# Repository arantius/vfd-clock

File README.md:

A six digit clock based on the IV-22 Vacuum Fluorescent Display tube.

A learning project for me, using vacuum fluorescent display tubes and the STM32 processor for the first time.

I personally built one of these, and ended up with lots of spare parts.
I sold a _very limited_ number of kits, made up mostly of those spares.
I have no plans to assemble nor sell any further kits.
If you are interested in building this clock yourself, check out the Bill of Materials below, and the issues tab.

# Bill of Materials

| Part | Reference(s) | Value | Example Manufacturer Part Number |
| ---- | ------------ | ----- | -------------------------------- |
| Battery Holder | BT1 | n/a | BU2032SM-BT-GTR |
| Chip Capacitor (0603) | C1, C2 | 4pF | - |
| Electrolytic Capacitor | C3, C4, C5, C6 | 47μF | 25YXF47MEFC5X11 |
| Chip Capacitor (0603) | C7 | 330pF | n/a |
| DC Jack | CON2 | - | EJ508A |
| DC Plug | - | - | PP3-002A |
| Diode | D1 | - | STPS130A |
| Inductor | L1 | 68μH | RCH8011NP-680L |
| Transistor | Q1, Q2 | - | MMBT4403LT1G |
| Resistor | R1 | 0.22Ω | LR1LJR22 |
| Chip Resistor (0603) | R2 | 12.4kΩ | - |
| Chip Resistor (0603) | R3 | 41.2kΩ | - |
| Chip Resistor (0603) | R4, R5 | 1kΩ | - |
| Variable Resistor | RV1 | 22kΩ | PVA2A223A01R00 [#1](https://github.com/arantius/vfd-clock/issues/1) |
| Piezo Speaker | SP1 | - | AT-1224-TWT-5V-2-R [#2](https://github.com/arantius/vfd-clock/issues/2) |
| Tactile Switch | SW1, SW2, SW3, SW4 | - | FSM6JSMA |
| Microcontroller | U1 | Maple Mini | - |
| 7-Segment Driver (16-SOIC) | U2, U3, U4, U5, U6, U7 | - | CD4056BM96 |
| Boost Regulator (8-SOIC) | U8 | - | MC34063ACD-TR |
| Volt Level Shifter (16-TSSOP) | U9, U10 | - | CD4504BPWR |
| VFD Display Tube | V1, V2, V3, V4, V5, V6 | - | IV-22 (a.k.a. IN-22, IИ-22) |
| Watch Crystal | X1 | 32.7680kHz | CFS-20632768DZBB |
| Optional GPS | - | - | NEO-6M |

Notes:
 * The official [Baite store on Aliexpress ](https://www.aliexpress.com/store/product/x/213957_1400682373.html) is a reliable source of cheap clone Maple Mini boards.
 * You'll also need 72 single-pin sockets for the tubes, these are most commonly/affordably available on eBay.  Look for "nixie pin socket".  (They're $0.20 each from DigiKey, but as low as $0.05 each in quantity from eBay.)  These sockets raise the tube off the board so that the vaccum seal "nipple" has some room.  Plus the ability to remove and replace tubes is nice!
 * The optional GPS module, if used, should have an 0.1" four pin header of: Vcc, RX, TX, GND in that order.  I used a "Ublox NEO-6M" module.
 * The battery (and its) holder is optional.  If you don't mind losing the time when you unplug you don't need it.

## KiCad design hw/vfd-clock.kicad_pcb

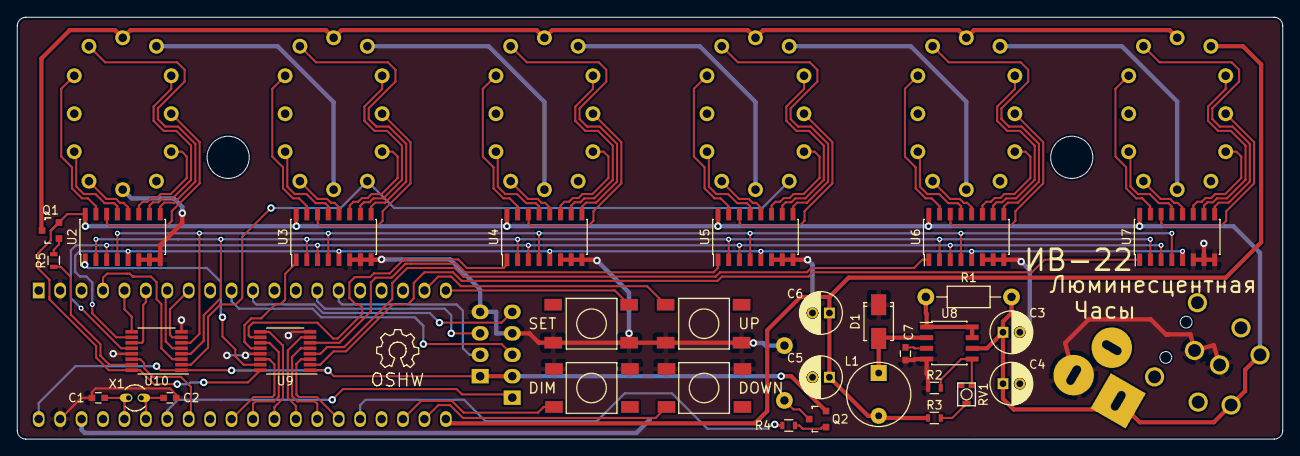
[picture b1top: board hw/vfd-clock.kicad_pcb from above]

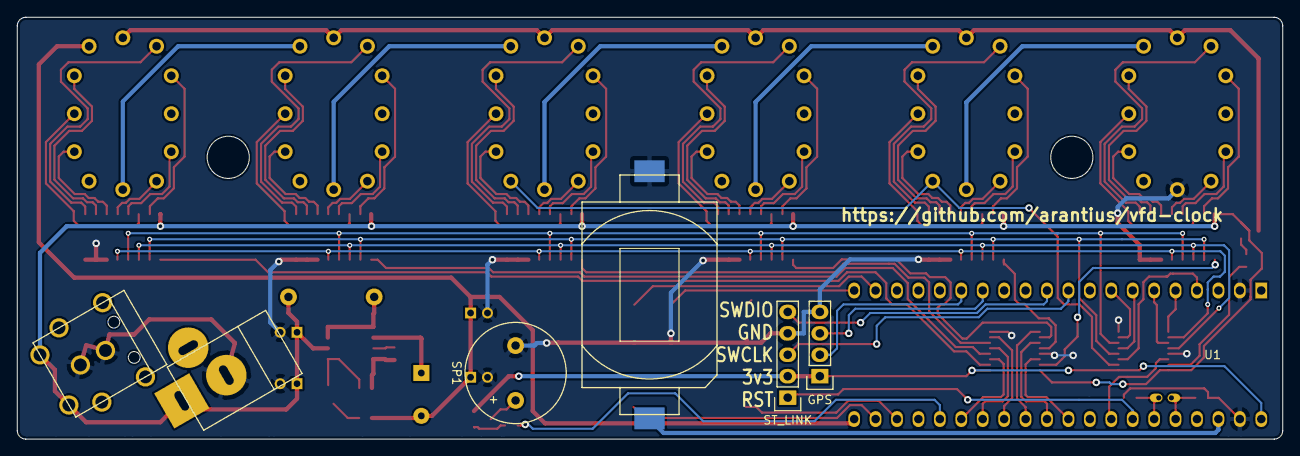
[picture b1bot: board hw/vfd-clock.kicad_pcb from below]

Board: 2 copper layers, 150.0 x 50.0 mm, 46 parts (7 on the bottom side), 97 nets.

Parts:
BT1: COIN_BATT; BATT2032-1060TR
C1, C2: 4p; C_0603
C3, C4, C5, C6: 47u; C_Radial_D5_L11_P2
C7: 330p; C_0603
CON1: BARREL_JACK_2; JACK_ALIM
CON2: BARREL_JACK_2; OCT_JACK
D1: DIODESCH; Diode-SMA_Standard
L1: 68u; INDUCTOR_V
M1, M2: MountingHole_4-5mm; MountingHole_5mm
P1: ST_LINK; Pin_Header_Straight_1x05
P2: GPS; Pin_Header_Straight_1x04
Q1, Q2: PNP; MMBT4403L
R1: 0.22; Resistor_Horizontal_RM10mm
R2: 12.4k; R_0603
R3: 54.9k; R_0603
R4, R5: 1k; R_0603
RV1: 4k7; PVA2_POT
SP1: SPEAKER; AT-1224-TWT
SW1: SET; SMD_TACT_6mm
SW2: UP; SMD_TACT_6mm
SW3: DOWN; SMD_TACT_6mm
SW4: DIM; SMD_TACT_6mm
U1: Maple_Mini_(BTE14-07)
U2, U3, U4, U5, U6, U7: CD4056; SOIC-16_3.9x9.9mm_Pitch1.27mm
U8: MC34063; SOIC-8_3.9x4.9mm_Pitch1.27mm
U9, U10: CD4504; TSSOP-16_4.4x5mm_Pitch0.65mm
V1, V2, V3, V4, V5, V6: IV-22; DISP_IV-22_1PIN_SOCKET
X1: CRYSTAL; Crystal_Round_Vertical_3mm_BigPad

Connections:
/3v3: P1.2, P2.1, Q2.1, U1.40, U9.1, U10.1
/7v2: C5.1, C6.1, L1.2, R3.2, U1.21, V6.1
/19v5: C3.1, C4.1, CON1.1, CON2.1, Q1.1, R1.1, U2.16, U3.16, U4.16, U5.16, U6.16, U7.16, U8.6, U9.16, U10.16
/A1: U2.9, V1.11
/A2: U3.9, V2.11
/A3: U4.9, V3.11
/A4: U5.9, V4.11
/A5: U6.9, V5.11
/A6: U7.9, V6.11
/B1: U2.10, V1.2
/B2: U3.10, V2.2
/B3: U4.10, V3.2
/B4: U5.10, V4.2
/B5: U6.10, V5.2
/B6: U7.10, V6.2
/BTN_DIM: SW4.1, U1.23
/BTN_DN: SW3.1, U1.22
/BTN_SET: SW1.1, U1.20
/BTN_UP: SW2.1, U1.19
/BUZ: R4.2, U1.25
/C1: U2.11, V1.4
/C2: U3.11, V2.4
/C3: U4.11, V3.4
/C4: U5.11, V4.4
/C5: U6.11, V5.4
/C6: U7.11, V6.4
/D1: U2.12, V1.7
/D2: U3.12, V2.7
/D3: U4.12, V3.7
/D4: U5.12, V4.7
/D5: U6.12, V5.7
/D6: U7.12, V6.7
/DAH: U2.5, U3.5, U4.5, U5.5, U6.5, U7.5, U10.10
/DAL: U1.5, U10.9
/DBH: U2.3, U3.3, U4.3, U5.3, U6.3, U7.3, U10.12
/DBL: U1.6, U10.11
/DCH: U2.2, U3.2, U4.2, U5.2, U6.2, U7.2, U10.4
/DCL: U1.7, U10.5
/DDH: U2.4, U3.4, U4.4, U5.4, U6.4, U7.4, U10.6
/DDL: U1.8, U10.7
/DPH: U10.2, V2.5, V4.5
/DPL: U1.4, U10.3
/E1: U2.13, V1.8
/E2: U3.13, V2.8
/E3: U4.13, V3.8
/E4: U5.13, V4.8
/E5: U6.13, V5.8
/E6: U7.13, V6.8
/F1: U2.15, V1.10
/F2: U3.15, V2.10
/F3: U4.15, V3.10
/F4: U5.15, V4.10
/F5: U6.15, V5.10
/F6: U7.15, V6.10
/FIL1: V1.1, V2.6
/FIL2: V2.1, V3.6
/FIL3: V3.1, V4.6
/FIL4: V4.1, V5.6
/FIL5: V5.1, V6.6
/G1: U2.14, V1.3
/G2: U3.14, V2.3
/G3: U4.14, V3.3
/G4: U5.14, V4.3
/G5: U6.14, V5.3
/G6: U7.14, V6.3
/GND: BT1.2, C1.2, C2.2, C3.2, C4.2, C5.2, C6.2, C7.1, CON1.2, CON2.2, D1.1, P1.4, P2.4, R2.2, SP1.2, SW1.2, SW2.2, SW3.2, SW4.2, U1.2, U1.39, U2.6, U2.7, U2.8, U3.6, U3.7, U3.8, U4.6, U4.7, U4.8, U5.6, U5.7, U5.8, U6.6, U6.7, U6.8, U7.6, U7.7, U7.8, U8.4, U9.8, U9.13, U10.8, U10.13, V1.6
/GPS_RX: P2.2, U1.15
/GPS_TX: P2.3, U1.14
/GRID: Q1.3, V1.12, V2.12, V3.12, V4.12, V5.12, V6.12
/GRIDH: R5.2, U10.15
/GRIDL: U1.33, U10.14
/REG_HI: R1.2, U8.1, U8.7, U8.8
/RST: P1.1, U1.34
/STROBE1H: U2.1, U9.15
/STROBE1L: U1.31, U9.14
/STROBE2H: U3.1, U9.12
/STROBE2L: U1.30, U9.11
/STROBE3H: U4.1, U9.10
/STROBE3L: U1.29, U9.9
/STROBE4H: U5.1, U9.6
/STROBE4L: U1.28, U9.7
/STROBE5H: U6.1, U9.4
/STROBE5L: U1.27, U9.5
/STROBE6H: U7.1, U9.2
/STROBE6L: U1.26, U9.3
/SWCLK: P1.3, U1.10
/SWDIO: P1.5, U1.11
/Vbat: BT1.1, U1.38
unnamed: C1.1, U1.36, X1.1
unnamed: C2.1, U1.35, X1.2
unnamed: C7.2, U8.3
unnamed: D1.2, L1.1, U8.2
unnamed: Q1.2, R5.1
unnamed: Q2.2, R4.1
unnamed: Q2.3, SP1.1
unnamed: R2.1, RV1.1, U8.5
unnamed: R3.1, RV1.2

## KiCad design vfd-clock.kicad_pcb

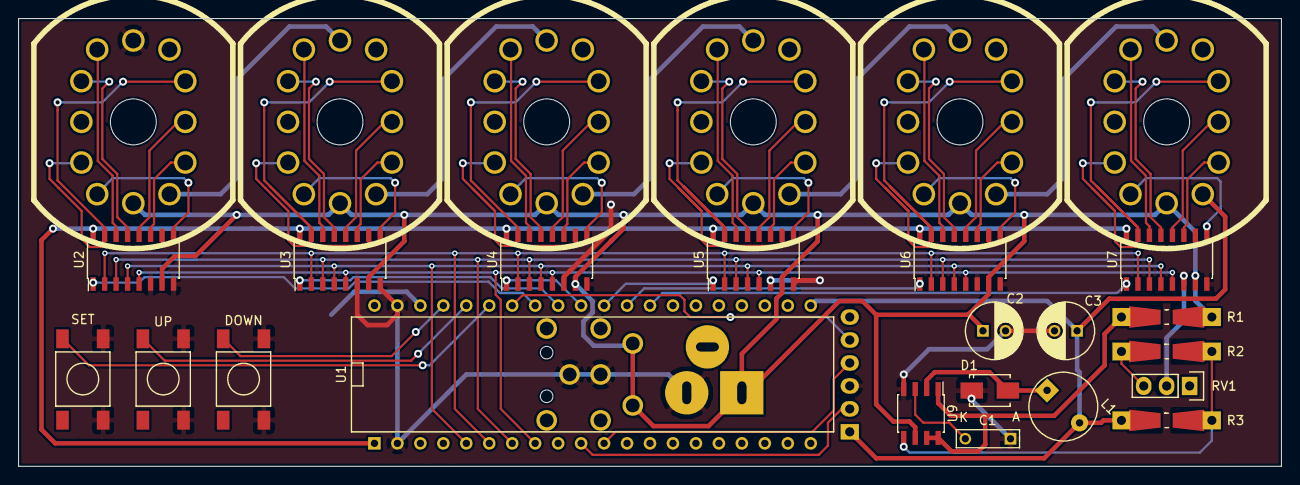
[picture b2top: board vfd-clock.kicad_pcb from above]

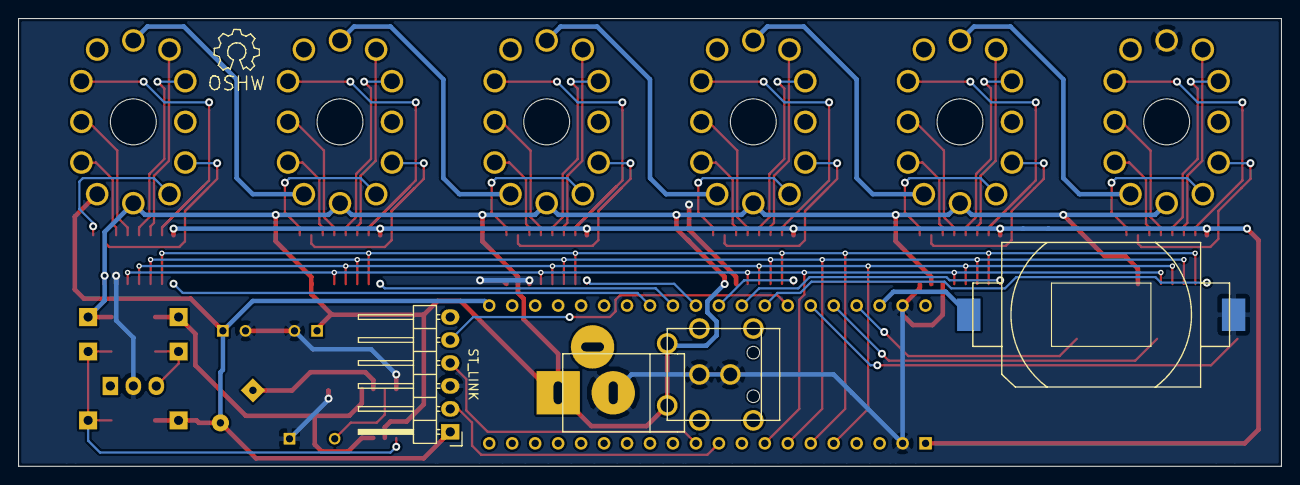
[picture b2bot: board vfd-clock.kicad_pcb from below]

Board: 2 copper layers, 139.7 x 49.5 mm, 30 parts (4 on the bottom side), 73 nets.

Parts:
BT1: COIN_BATT; BATT2032-1060TR
C1: 330p; C_Rect_L7_W2_P5
C2, C3: 100u; C_Radial_D6.3_L11.2_P2.5
CON1: BARREL_JACK_2; JACK_ALIM
CON2: BARREL_JACK_2; OCT_JACK
D1: DIODESCH; Diode-SMA_Standard
L1: 68u; INDUCTOR_V
P1: ST_LINK; Pin_Header_Angled_1x06
R1: 0.22; Resistor_SMD+THTuniversal_0805to1206_RM10_HandSoldering
R2: 12k; Resistor_SMD+THTuniversal_0805to1206_RM10_HandSoldering
R3: 59.5k; Resistor_SMD+THTuniversal_0805to1206_RM10_HandSoldering
RV1: 1k; Pin_Header_Straight_1x03
SW1: SET; SMD_TACT_6mm
SW2: UP; SMD_TACT_6mm
SW3: DOWN; SMD_TACT_6mm
U1: Maple_Mini_(BTE14-07); DIP-40__600
U2, U3, U4, U5, U6, U7: CD4056; SOIC-16_3.9x9.9mm_Pitch1.27mm
U9: MC34063; SOIC-8_3.9x4.9mm_Pitch1.27mm
V1, V2, V3, V4, V5, V6: IV-22; DISP_IV-22_SOCKET

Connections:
/3v3: U1.1, U2.16, U3.16, U4.16, U5.16, U6.16, U7.16
/7v2: C3.1, L1.2, P1.1, R3.1, U1.21, V6.5
/19v5: C2.1, CON1.1, CON2.1, R1.1, U2.7, U3.7, U4.7, U5.7, U6.7, U7.7, U9.6, V1.6, V2.6, V3.6, V4.6, V5.6, V6.6
/BTN_DN: SW3.1, U1.37
/BTN_SET: SW1.1, U1.35
/BTN_UP: SW2.1, U1.36
/DA: U1.8, U2.5, U3.5, U4.5, U5.5, U6.5, U7.5
/DB: U1.7, U2.3, U3.3, U4.3, U5.3, U6.3, U7.3
/DC: U1.6, U2.2, U3.2, U4.2, U5.2, U6.2, U7.2
/DD: U1.5, U2.4, U3.4, U4.4, U5.4, U6.4, U7.4
/FIL1: V1.5, V2.12
/FIL2: V2.5, V3.12
/FIL3: V3.5, V4.12
/FIL4: V4.5, V5.12
/FIL5: V5.5, V6.12
/GND: BT1.2, C1.1, C2.2, C3.2, CON1.2, CON2.2, D1.1, P1.3, RV1.2, SW1.2, SW2.2, SW3.2, U1.2, U1.39, U2.6, U2.8, U3.6, U3.8, U4.6, U4.8, U5.6, U5.8, U6.6, U6.8, U7.6, U7.8, U9.4, V1.12
/REG_HI: R1.2, U9.1, U9.7, U9.8
/RST: P1.5, U1.34
/STROBE1: U1.33, U2.1
/STROBE2: U1.32, U3.1
/STROBE3: U1.31, U4.1
/STROBE4: U1.30, U5.1
/STROBE5: U1.29, U6.1
/STROBE6: U1.28, U7.1
/SWCLK: P1.2, U1.10
/SWDIO: P1.4, U1.11
/Vbat: BT1.1, U1.38
unnamed: C1.2, U9.3
unnamed: D1.2, L1.1, U9.2
unnamed: R2.1, RV1.3
unnamed: R2.2, R3.2, U9.5
unnamed: U2.9, V1.7
unnamed: U2.10, V1.8
unnamed: U2.11, V1.4
unnamed: U2.12, V1.3
unnamed: U2.13, V1.10
unnamed: U2.14, V1.11
unnamed: U2.15, V1.2
unnamed: U3.9, V2.7
unnamed: U3.10, V2.8
unnamed: U3.11, V2.4
unnamed: U3.12, V2.3
unnamed: U3.13, V2.10
unnamed: U3.14, V2.11
unnamed: U3.15, V2.2
unnamed: U4.9, V3.7
unnamed: U4.10, V3.8
unnamed: U4.11, V3.4
unnamed: U4.12, V3.3
unnamed: U4.13, V3.10
unnamed: U4.14, V3.11
unnamed: U4.15, V3.2
unnamed: U5.9, V4.7
unnamed: U5.10, V4.8
unnamed: U5.11, V4.4
unnamed: U5.12, V4.3
unnamed: U5.13, V4.10
unnamed: U5.14, V4.11
unnamed: U5.15, V4.2
unnamed: U6.9, V5.7
unnamed: U6.10, V5.8
unnamed: U6.11, V5.4
unnamed: U6.12, V5.3
unnamed: U6.13, V5.10
unnamed: U6.14, V5.11
unnamed: U6.15, V5.2
unnamed: U7.9, V6.7
unnamed: U7.10, V6.8
unnamed: U7.11, V6.4
unnamed: U7.12, V6.3
unnamed: U7.13, V6.10
unnamed: U7.14, V6.11
unnamed: U7.15, V6.2

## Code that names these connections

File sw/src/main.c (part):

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#define BTN_MAPLE_PIN GPIO_Pin_8

#define BTN_PORT GPIOB
#define BTN_DIM_PIN GPIO_Pin_10
#define BTN_SET_PIN GPIO_Pin_12
#define BTN_UP_PIN GPIO_Pin_13
#define BTN_DN_PIN GPIO_Pin_11
typedef enum {BTN_NONE, BTN_MAPLE, BTN_UP, BTN_DOWN, BTN_DIM, BTN_SET} ButtonId;
#define BTN_ALL_PINS (BTN_MAPLE_PIN|BTN_DIM_PIN|BTN_SET_PIN|BTN_UP_PIN|BTN_DN_PIN)

#define DATA_PORT GPIOB
#define DA_PIN GPIO_Pin_6
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#define DP_PIN GPIO_Pin_7

#define STROBE_PORT GPIOA
#define STROBE1_PIN GPIO_Pin_2
#define STROBE2_PIN GPIO_Pin_3
#define STROBE3_PIN GPIO_Pin_4
#define STROBE4_PIN GPIO_Pin_5
#define STROBE5_PIN GPIO_Pin_6
#define STROBE6_PIN GPIO_Pin_7
#define STROBE_ALL_PINS ( \
    STROBE1_PIN | STROBE2_PIN | STROBE3_PIN \
    | STROBE4_PIN | STROBE5_PIN | STROBE6_PIN)

#define GRID_PORT GPIOA
#define GRID_PIN GPIO_Pin_0
#define BUZ_PORT GPIOB
#define BUZ_PIN GPIO_Pin_0

#define DIGIT_L 10
#define DIGIT_H 11
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// Amount to change the current time by, when setting this digit up/down.
const uint16_t gSettingChange[6] = {0, 3600, 600, 60, 10, 1};
const uint16_t gStrobePins[6] = {
    STROBE1_PIN, STROBE2_PIN, STROBE3_PIN,
    STROBE4_PIN, STROBE5_PIN, STROBE6_PIN};

// \\ // \\ // \\ // \\ // \\ // \\ // \\ // \\ // \\ // \\ // \\ // \\ // \\ //

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  GPIO_InitStructure.GPIO_Speed = GPIO_Speed_10MHz;

  // Port A, output.
  GPIO_InitStructure.GPIO_Pin = STROBE1_PIN | STROBE2_PIN | STROBE3_PIN
      | STROBE4_PIN | STROBE5_PIN | STROBE6_PIN;
  GPIO_InitStructure.GPIO_Mode = GPIO_Mode_Out_PP;  // Push-pull output.
  GPIO_Init(GPIOA, &GPIO_InitStructure);

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  GPIO_InitStructure.GPIO_Mode = GPIO_Mode_IPD;  // Input, pull down.
  GPIO_Init(GPIOB, &GPIO_InitStructure);
  GPIO_InitStructure.GPIO_Pin =
      BTN_DIM_PIN | BTN_SET_PIN | BTN_UP_PIN | BTN_DN_PIN;
  GPIO_InitStructure.GPIO_Mode = GPIO_Mode_IPU;  // Input, pull up.
  GPIO_Init(GPIOB, &GPIO_InitStructure);
  // Port B, output.
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  GPIO_InitTypeDef GPIO_InitStructure;
  GPIO_InitStructure.GPIO_Speed = GPIO_Speed_10MHz;
  GPIO_InitStructure.GPIO_Mode = GPIO_Mode_AF_PP;
  GPIO_InitStructure.GPIO_Pin = GRID_PIN;
  GPIO_Init(GRID_PORT, &GPIO_InitStructure);
  GPIO_InitStructure.GPIO_Pin = BUZ_PIN;
  GPIO_Init(BUZ_PORT, &GPIO_InitStructure);

  // Time base configuration;
  TIM_TimeBaseInitTypeDef  TIM_TimeBaseStructure;
  TIM_TimeBaseStructure.TIM_ClockDivision = TIM_CKD_DIV1;
  TIM_TimeBaseStructure.TIM_CounterMode = TIM_CounterMode_Up;

  // Grid PWM is on PA0 (D11), this is timer 2 channel 1.
  // 72MHz system clock / 1800 / 80 = 500Hz
  TIM_TimeBaseStructure.TIM_Period = 80;
  TIM_TimeBaseStructure.TIM_Prescaler = 1800;
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  uint8_t btnPressed = 0;
  uint16_t btns = GPIO_ReadInputData(BTN_PORT) & BTN_ALL_PINS;
  if ((btns & BTN_MAPLE_PIN) == BTN_MAPLE_PIN) btnPressed = BTN_MAPLE;
  else if ((btns & BTN_DIM_PIN) == 0) btnPressed = BTN_DIM;
  else if ((btns & BTN_DN_PIN) == 0) btnPressed = BTN_DOWN;
  else if ((btns & BTN_UP_PIN) == 0) btnPressed = BTN_UP;
  else if ((btns & BTN_SET_PIN) == 0) btnPressed = BTN_SET;
  if (btnPressed && gButtonPending == btnPressed) {
    if (gButtonDebounce > 10) {
      // Button already activated, still held, do nothing.
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  GPIO_WriteBit(LED_PORT, LED_PIN, RESET);

  // Disable buzzer.
  GPIO_WriteBit(BUZ_PORT, BUZ_PIN, RESET);
  TIM_Cmd(TIM3, DISABLE);

  backupLoad();
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
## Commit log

2015-05-31 initial commit; with maple mini library component
2015-05-31 add CD4504 level shifters
2015-05-31 add CD4543
2015-05-31 add IV-22
2015-05-31 various bits of the schematic wired up
2015-05-31 remove backup file
2015-06-01 schematic progress, board positioning
2015-06-01 tubes, data bus: routed
2015-06-01 first fully routed revision
2015-06-01 second redundant power connector footprint
    (I expect to only ever populate one or the other.)
2015-06-01 add buttons to set time
2015-06-05 lots of rerouting, buttons, part switches
    surface mount!
2015-07-14 create 'hw' directory beside 'sw'
2015-07-15 Major hardware rework.
    With discrete voltage level shifters, buzzer, pins for a GPS module
    addon.
2015-07-15 slim main.c
2015-07-15 Blinky project base.
    "New project" template from GNU Arm Eclipse plugins.
2015-07-15 set counter value AND interrupt once per second!!!
2015-07-15 Set RTC prescaler correctly.
    Add an extra #if branch because it has to come after WaitForSynchro()!
2015-07-15 use mini's button to set a counter value
2015-07-15 crappy working version via systick
2015-07-15 start to do button/display I/O
    Only thing that works for sure is the LED test
2015-07-15 rtc init? doesn't fire interrupts
2015-07-15 duh, enable GPIO port B !
2015-07-15 Doc note.
2015-07-15 add sw LICENSE
2015-07-15 more minimal, RTC interrupt fires
    way too often though???
2015-07-15 interrupt handler only sets a few global vars
2015-07-15 get rid of unused main() args
    and the noisy GCC pragmas to silence the warnings
2015-07-16 various small tweaks
    including switch the VFD tube outline from silkscreen to fab layer
2015-07-16 Fix VFD pinout.
2015-07-16 VFD trace tweak, label font size
2015-07-17 last level shifter output lights decimal points
    specifically the 2nd and 4th, i.e. between the hours/minutes and
    minutes/seconds
2015-07-19 mount holes, tweaks to ground fill, gerbers
2015-07-19 Sketchup framework for stand design
2015-07-19 Complete design for plastic stand.
2015-07-19 move mount holes to work well with plastic stand
2015-07-19 fix missing silksreen text
2015-07-20 screw joints for horizontal support
2015-07-21 fix transistor pin orientation
2015-07-21 widen battery terminals for easier hand soldering
2015-07-21 fix buzzer pin width
2015-07-22 volt shifters ssop->tssop
2015-07-22 update gerbers
2015-07-22 rotate power jacks for plug clearance
2015-07-22 Add README, LICENSE, github link.
2015-07-22 realign logo text
    to miss recently moved power jack holes
2015-07-24 Update maple mini but/led pins.
2015-07-25 WIP working PWM output
2015-07-25 move grid/buz outputs to distinct PWM timer pins
    rearrange a few traces for better ground fill and some silkscreen text
    as well
2015-07-25 rounded corners
2015-07-25 various track tweaks
2015-07-25 updated gerbers
2015-07-27 Refine initGpio().
    * Simplify.
    * Add all new pins (buz, grid, DP).
    * Make all #defines match new hardware layout.
2015-07-27 Coalesce RTC and Timer code.
2015-07-27 defines for maple built ins
2015-07-28 fix: expose copper/pull back solder mask around VFD pins on bottom layer
2015-07-30 remove unused SysTick
2015-07-30 Calculate time digits, set all pins appropriately.
2015-07-30 More efficient strobe pin setting.
2015-07-30 Shorter strobe delay.
    Driving at 20v instead of 3v3 means the chip requires less time to load the data pins.
2015-07-31 Keep strobe lines low while setting data lines.
2015-07-31 Collapse to one DATA_PORT value.
2015-07-31 Put pulseStrobeLine() after functions it calls.
2015-08-01 Disable JTAG, to enable PB3/PB4 (for lines DC, DD).
2015-08-01 Configure release build to match debug build.
    Hopefully ...
2015-08-01 Index gStrobePins correctly.
    The strobeLine value is 1-indexed (0 meaning none), so -1 to address the
    zero-indexed array!
2015-08-01 Adjust strobeWait().
2015-08-02 One atomic write to set data pins.
2015-08-02 tweak initial blanking
2015-08-02 Drive all five buttons via interrupts.
    TODO: debounce.
2015-08-02 Helper: setDisplay()
2015-08-02 Named constants for non-digit "digit" values.
2015-08-02 Basic time setting via button handling
2015-08-02 Update gBlinkStatus via SysTick handler.
2015-08-03 fix values for a few passives
2015-08-03 fix buzzer size layout
2015-08-06 Comletely disable the buzzer.
    It works! And I don't want it buzzing nonstop, until I write code to make it beep and bloop correctly.
2015-08-06 Remove the once-per-second LED blink.
2015-08-06 Functional dim button.
2015-08-06 Blink decimal points each second.
2015-08-06 Add release build.
2015-08-07 Update stand for power cord clearance.
    Also more space for screw (threads) to fit through in vertical legs.
2015-08-07 Faster systick interrupt.
    Used for:
    * Polling/debouncing buttons.
    * Blinking DP on half seconds.
    * Still blinking digit-to-set.
2015-08-07 Switch to external crystal for RTC.
2015-08-07 Updated release build.
2015-08-07 Regulator resistor divider value update.
    I picked the wrong base/pot values to set the regulator's output voltage; I can only set it from barely not too high to definitely too high.
    Switch to a relatively huge trimpot and a smaller base, to have a wider adjustment range.
2015-08-08 Don't reset the RTC counter at boot.
    So the battery backup will work!
2015-08-19 Try two: power-cord-compatible stand.
    After pushing so far back I decided to A) revert the left leg to how I
    started and B) loop around for more support in front of the cord. Also,
    both front feet are pulled forward for better tipping resistance. (Rear
    were positioned OK, but front were not out in front enough.)
2015-08-19 Forced 12 hour mode.
2015-08-19 Update release build.
2015-08-23 Add support for setting time by GPS.
    Plus setting the UTC offset, since GPS only provides UTC time.
2015-08-24 Redo GPS time support based on ZDA sentence.
2015-08-25 Create handleButtonPress() helper.
2015-08-25 Create handleDigits() helper.
2015-08-25 Create handleDisplay() helper.
2015-08-25 Clean up GPS handling.
    - Remove debugging LED light.
    - Maple button toggles GPS availability flag
    - Fix data poll ("frequency" value is only 0/1).
    - Correct utc offset display always.
    Also update release build.
2015-08-25 Save UTC offset and dim level in backup registers.
2017-01-02 Add BOM to README
    Plus some part/assembly notes.
2017-01-02 PNP transistors, not MOSFET
2017-01-02 Updated resistor values
2017-01-02 BOM update
    Mention the plug that mates with the jack, and that the battery is optional.

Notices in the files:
sw/src/main.c:
Copyright (C) 2015  Anthony Lieuallen
This program is free software: you can redistribute it and/or modify
it under the terms of the GNU General Public License as published by
the Free Software Foundation, either version 3 of the License, or
(at your option) any later version.
